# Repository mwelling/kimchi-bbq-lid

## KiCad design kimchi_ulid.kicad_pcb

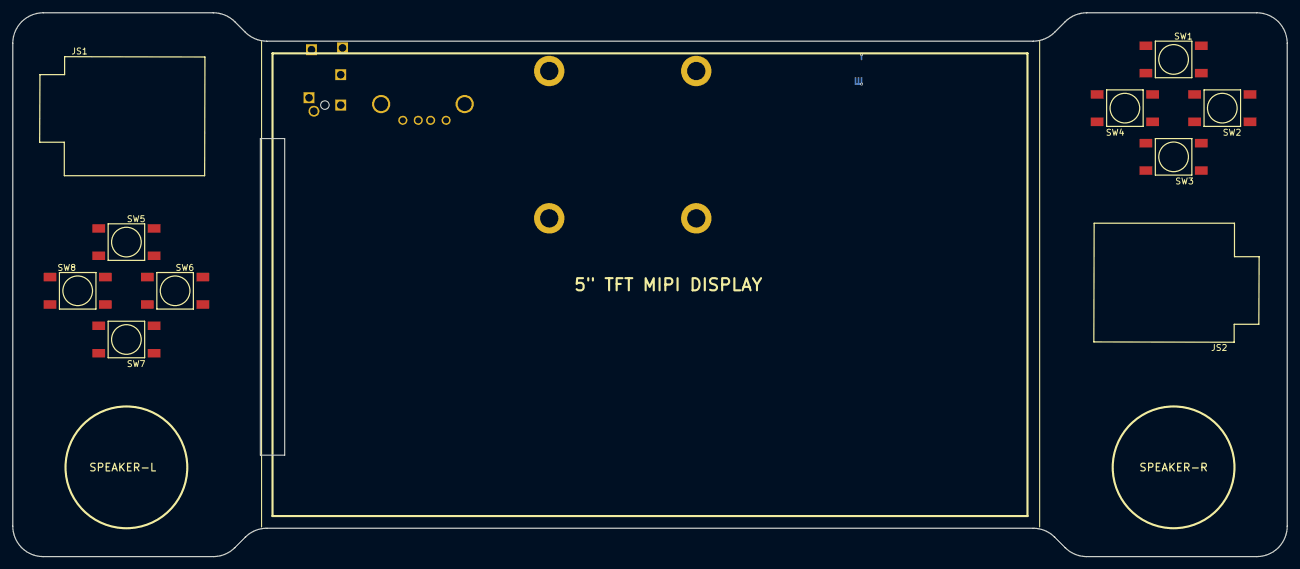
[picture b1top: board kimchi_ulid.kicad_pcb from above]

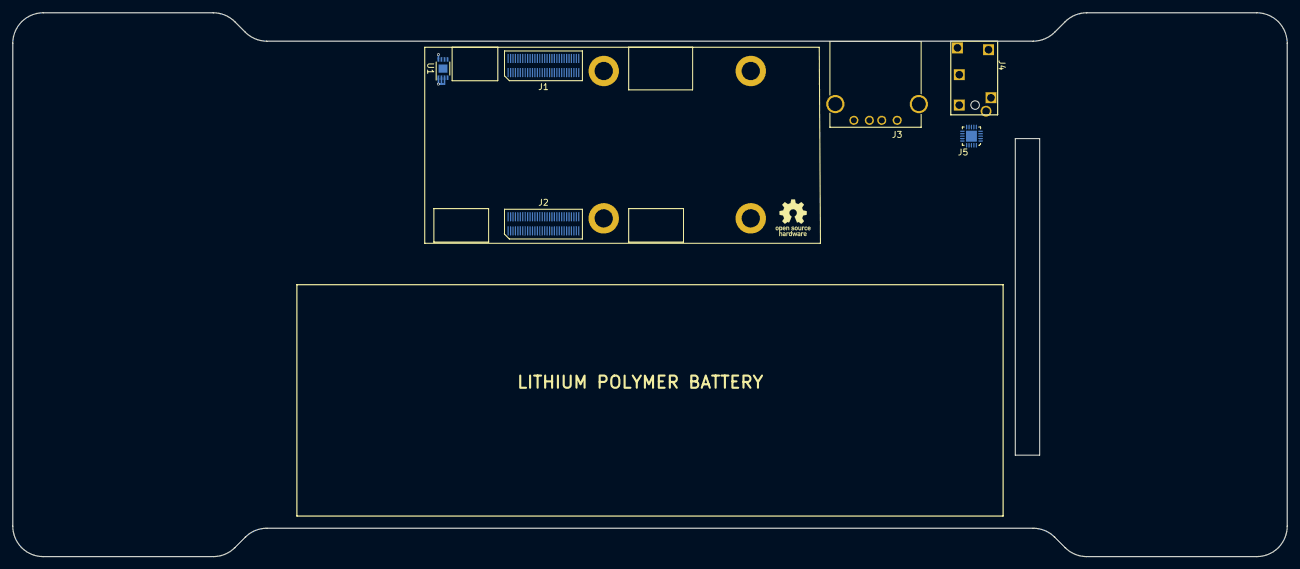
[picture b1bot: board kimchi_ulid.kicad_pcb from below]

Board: 4 copper layers, 209.3 x 89.3 mm, 21 parts (7 on the bottom side), 9 nets.

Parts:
H1, H2, H3, H4: MountingHole_Pad; MountingHole_3mm_Pad
J1, J2: DF40HC(3.5)-60DS
J3: KUSBX-AS1N-B; USB_A
J4: 54-00176
J5: SGTL5000XNLA3; QFN40P300X300X60-21N
JS1, JS2: Keyes_HW-504; Keyes_JoyStick
LOGO1: Logo_Open_Hardware_Small; OSHW-Logo_5.7x6mm_SilkScreen
SW1, SW2, SW3, SW4, SW5, SW6, SW7, SW8: TL3301NF260QG
U1: 24C32; DFN-8-1EP_3x2mm_P0.5mm_EP1.36x1.46mm

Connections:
GND: H1.1, H2.1, H3.1, H4.1, J1.11, J1.12, J1.13, J1.14, J1.51, J2.38, J2.39, J2.40, J2.41, J2.50, J2.51, J2.52, J2.53, J3.4, J3.5, U1.4, U1.7
I2C4_SCL: J1.16, U1.6
I2C4_SDA: J1.15, U1.5
USB2_DN: J1.59, J3.2
USB2_DP: J1.60, J3.3
USB2_VBUS: J1.57, J3.1
VDD_1V8: J2.42, J2.43, J2.44, J2.45
VDD_3V3: J2.54, J2.55, J2.56, J2.57, U1.1, U1.2, U1.3, U1.8
VDD_5V: J1.7, J1.8, J1.9, J1.10

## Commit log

2020-12-04 Clean up
2020-12-08 Board Shape
    Added board shape and mocked up location of Kimchi module and lipo battery solution.
2020-12-09 Mockup Progress
    Added standard SMT tactile switches to represent the button pad layout for both D-Pad and Face Buttons. Added dummy Analog Sticks for mockup purposes until we can get samples of the Nintendo Switch J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
